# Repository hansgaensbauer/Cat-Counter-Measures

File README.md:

# Cat-Counter-Measures
Counter Cat Countermeasures

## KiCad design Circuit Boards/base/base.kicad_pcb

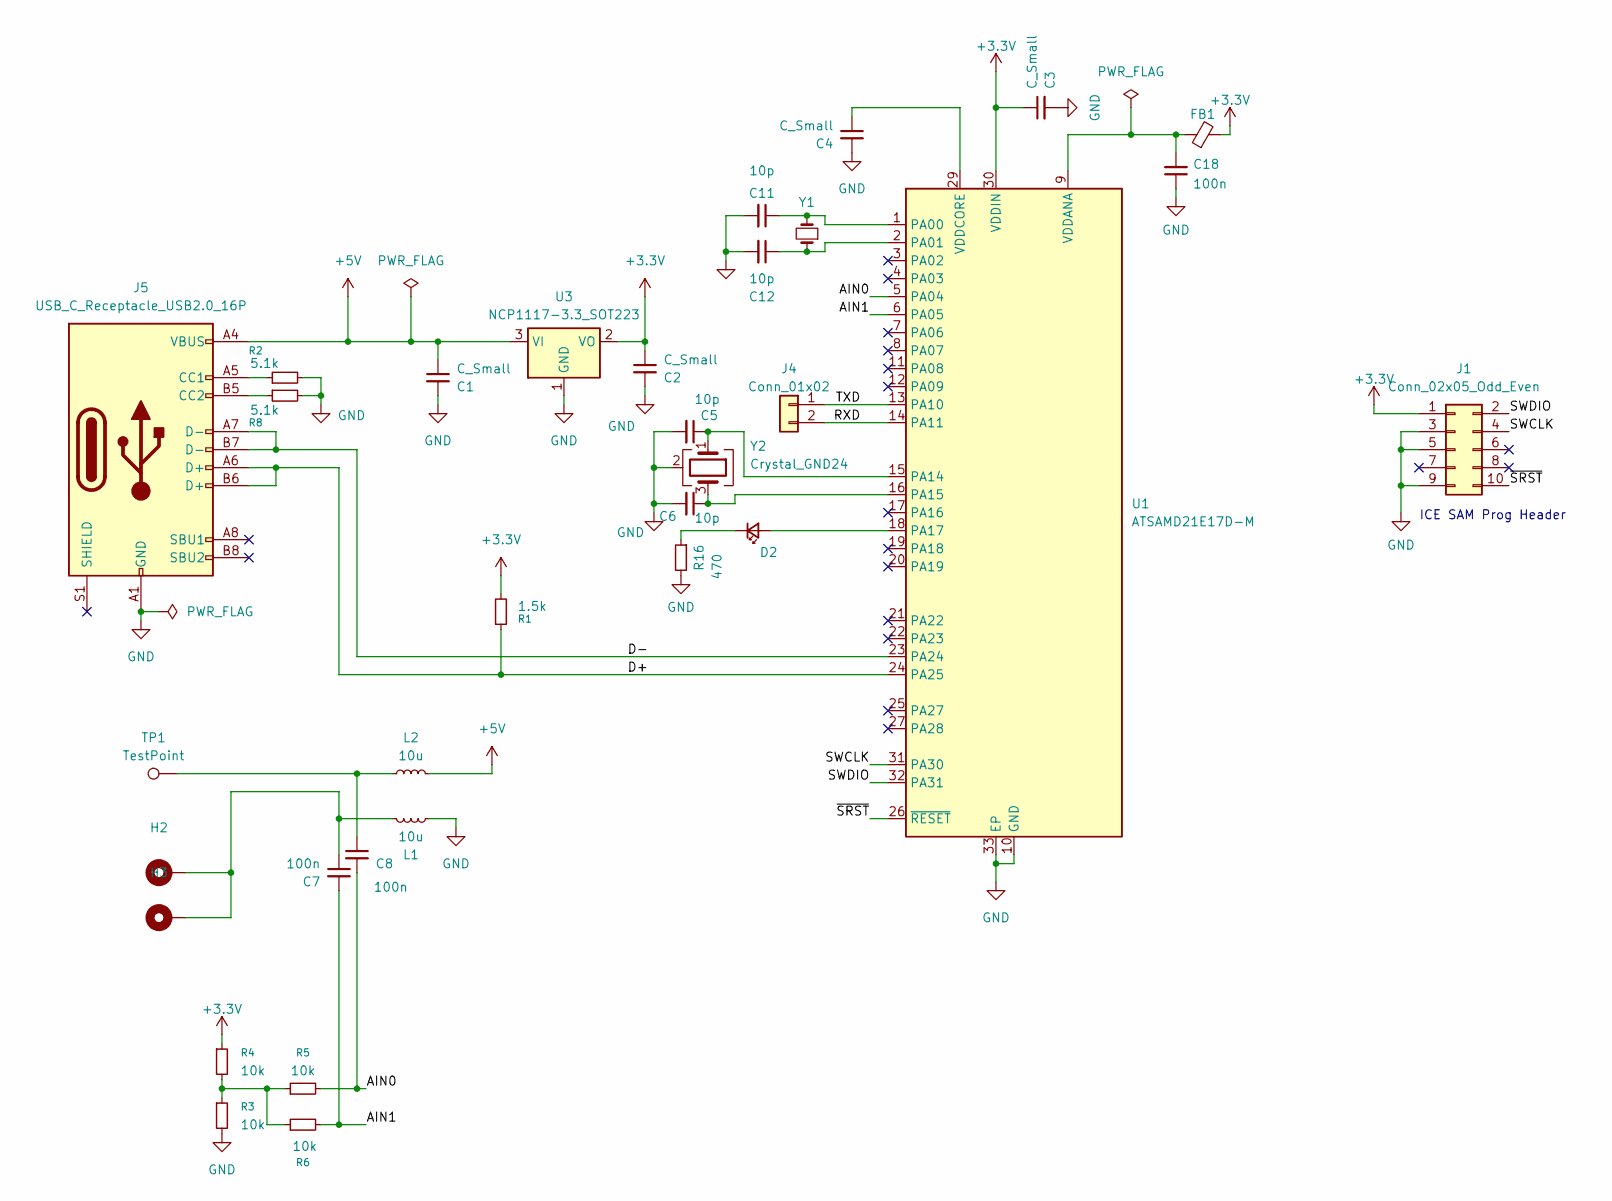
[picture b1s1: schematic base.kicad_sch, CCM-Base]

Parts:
C1, C2, C3, C4: C_Small; C_0603_1608Metric
C5, C6, C11, C12: 10p; C_0603_1608Metric
C7, C8, C18: 100n; C_0603_1608Metric
D2: LED_Small; LED_0805_2012Metric
FB1: FerriteBead_Small; R_0603_1608Metric
H2, H3: MountingHole_Pad; MountingHole_3.2mm_M3_ISO14580_Pad
J1: Conn_02x05_Odd_Even; PinHeader_2x05_P1.27mm_Vertical
J4: Conn_01x02; PinHeader_1x02_P2.54mm_Vertical
J5: USB_C_Receptacle_USB2.0_16P; USB_C_Receptacle_GCT_USB4085
L1, L2: 10u; L_0805_2012Metric
R1: 1.5k; R_0603_1608Metric
R2, R8: 5.1k; R_0603_1608Metric
R3, R4, R5, R6: 10k; R_0603_1608Metric
R16: 470; C_0603_1608Metric
TP1: TestPoint; TestPoint_THTPad_D2.0mm_Drill1.0mm
U1: ATSAMD21E17D-M; QFN-32-1EP_5x5mm_P0.5mm_EP3.6x3.6mm
U3: NCP1117-3.3_SOT223; SOT-223-3_TabPin2
Y1: Crystal_Small; Crystal_SMD_MicroCrystal_CM9V-T1A-2Pin_1.6x1.0mm
Y2: Crystal_GND24; Crystal_SMD_WE_CFPX-180-4Pin_3.2x2.5mm

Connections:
+3.3V: C2.1, C3.1, FB1.2, J1.1, R1.2, R4.1, U1.30 (VDDIN), U3.2 (VO)
+5V: C1.1, J5.A4 (VBUS), J5.A9 (VBUS), J5.B4 (VBUS), J5.B9 (VBUS), L2.1, U3.3 (VI)
/AIN0: C8.2, R5.2, U1.5 (PA04)
/AIN1: C7.2, R6.2, U1.6 (PA05)
/D+: J5.A6 (D+), J5.B6 (D+), R1.1, U1.24 (PA25)
/D-: J5.A7 (D-), J5.B7 (D-), U1.23 (PA24)
/RXD: J4.2, U1.14 (PA11)
/SWCLK: J1.4, U1.31 (PA30)
/SWDIO: J1.2, U1.32 (PA31)
/TXD: J4.1, U1.13 (PA10)
/~SRST: J1.10, U1.26 (~RESET)
GND: C1.2, C2.2, C3.2, C4.2, C5.2, C6.2, C11.2, C12.2, C18.1, J1.3, J1.5, J1.9, J5.A1 (GND), J5.A12 (GND), J5.B1 (GND), J5.B12 (GND), L1.1, R2.2, R3.2, R8.2, R16.2, U1.10 (GND), U1.28 (GND), U1.33 (EP), U3.1 (GND), Y2.2 (G), Y2.4 (G)
unnamed: C7.1, H2.1, H3.1, L1.2
unnamed: C8.1, L2.2, TP1.1
unnamed: D2.2 (A), U1.18 (PA17)
unnamed: D2.1 (K), R16.1
unnamed: J5.A5 (CC1), R2.1
unnamed: J5.B5 (CC2), R8.1
unnamed: R3.1, R4.2, R5.1, R6.1
unnamed: C11.1, U1.1 (PA00), Y1.2
unnamed: C12.1, U1.2 (PA01), Y1.1
unnamed: C5.1, U1.15 (PA14), Y2.1
unnamed: C6.1, U1.16 (PA15), Y2.3
unnamed: C18.2, FB1.1, U1.9 (VDDANA)
unnamed: C4.1, U1.29 (VDDCORE)

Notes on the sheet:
ICE SAM Prog Header

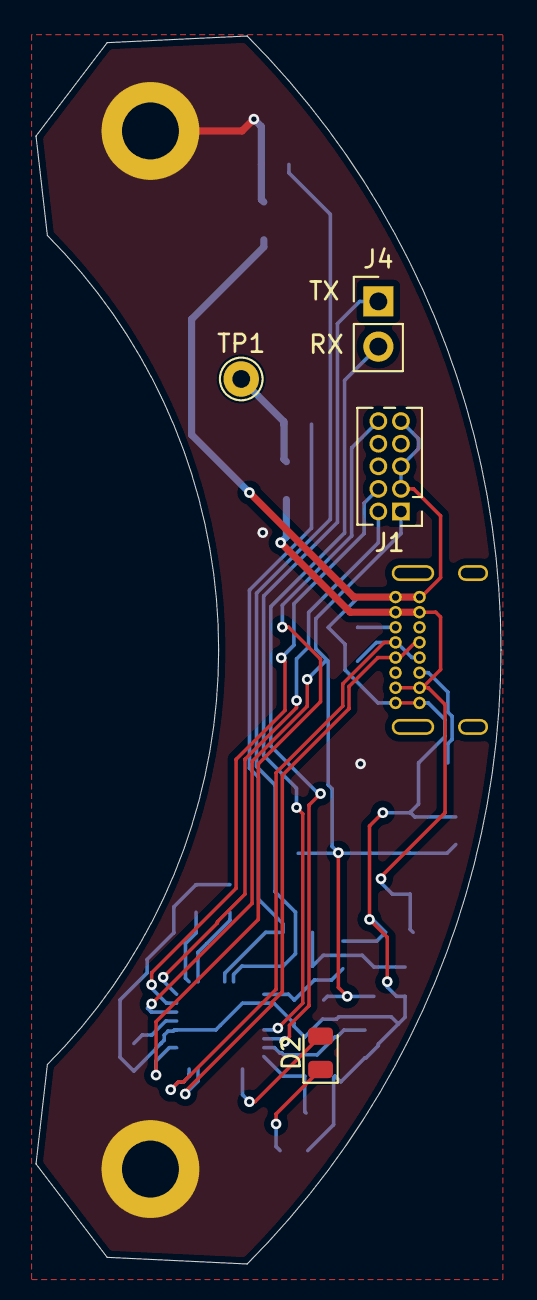
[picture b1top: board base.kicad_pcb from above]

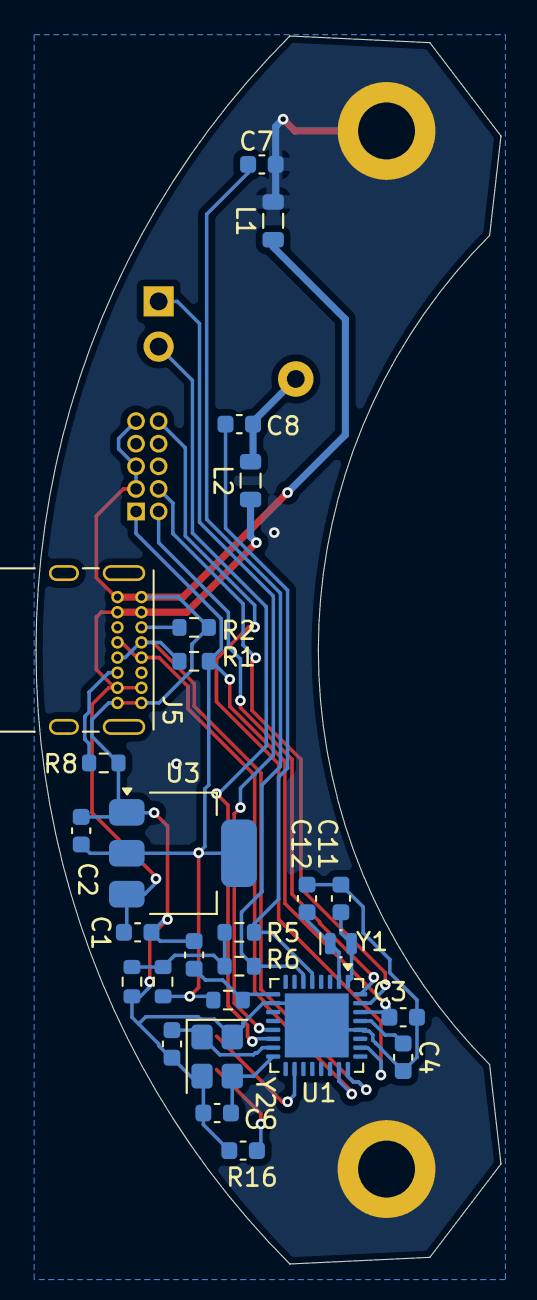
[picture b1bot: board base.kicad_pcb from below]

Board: 2 copper layers, 26.1 x 69.0 mm, 33 parts (27 on the bottom side), 25 nets.

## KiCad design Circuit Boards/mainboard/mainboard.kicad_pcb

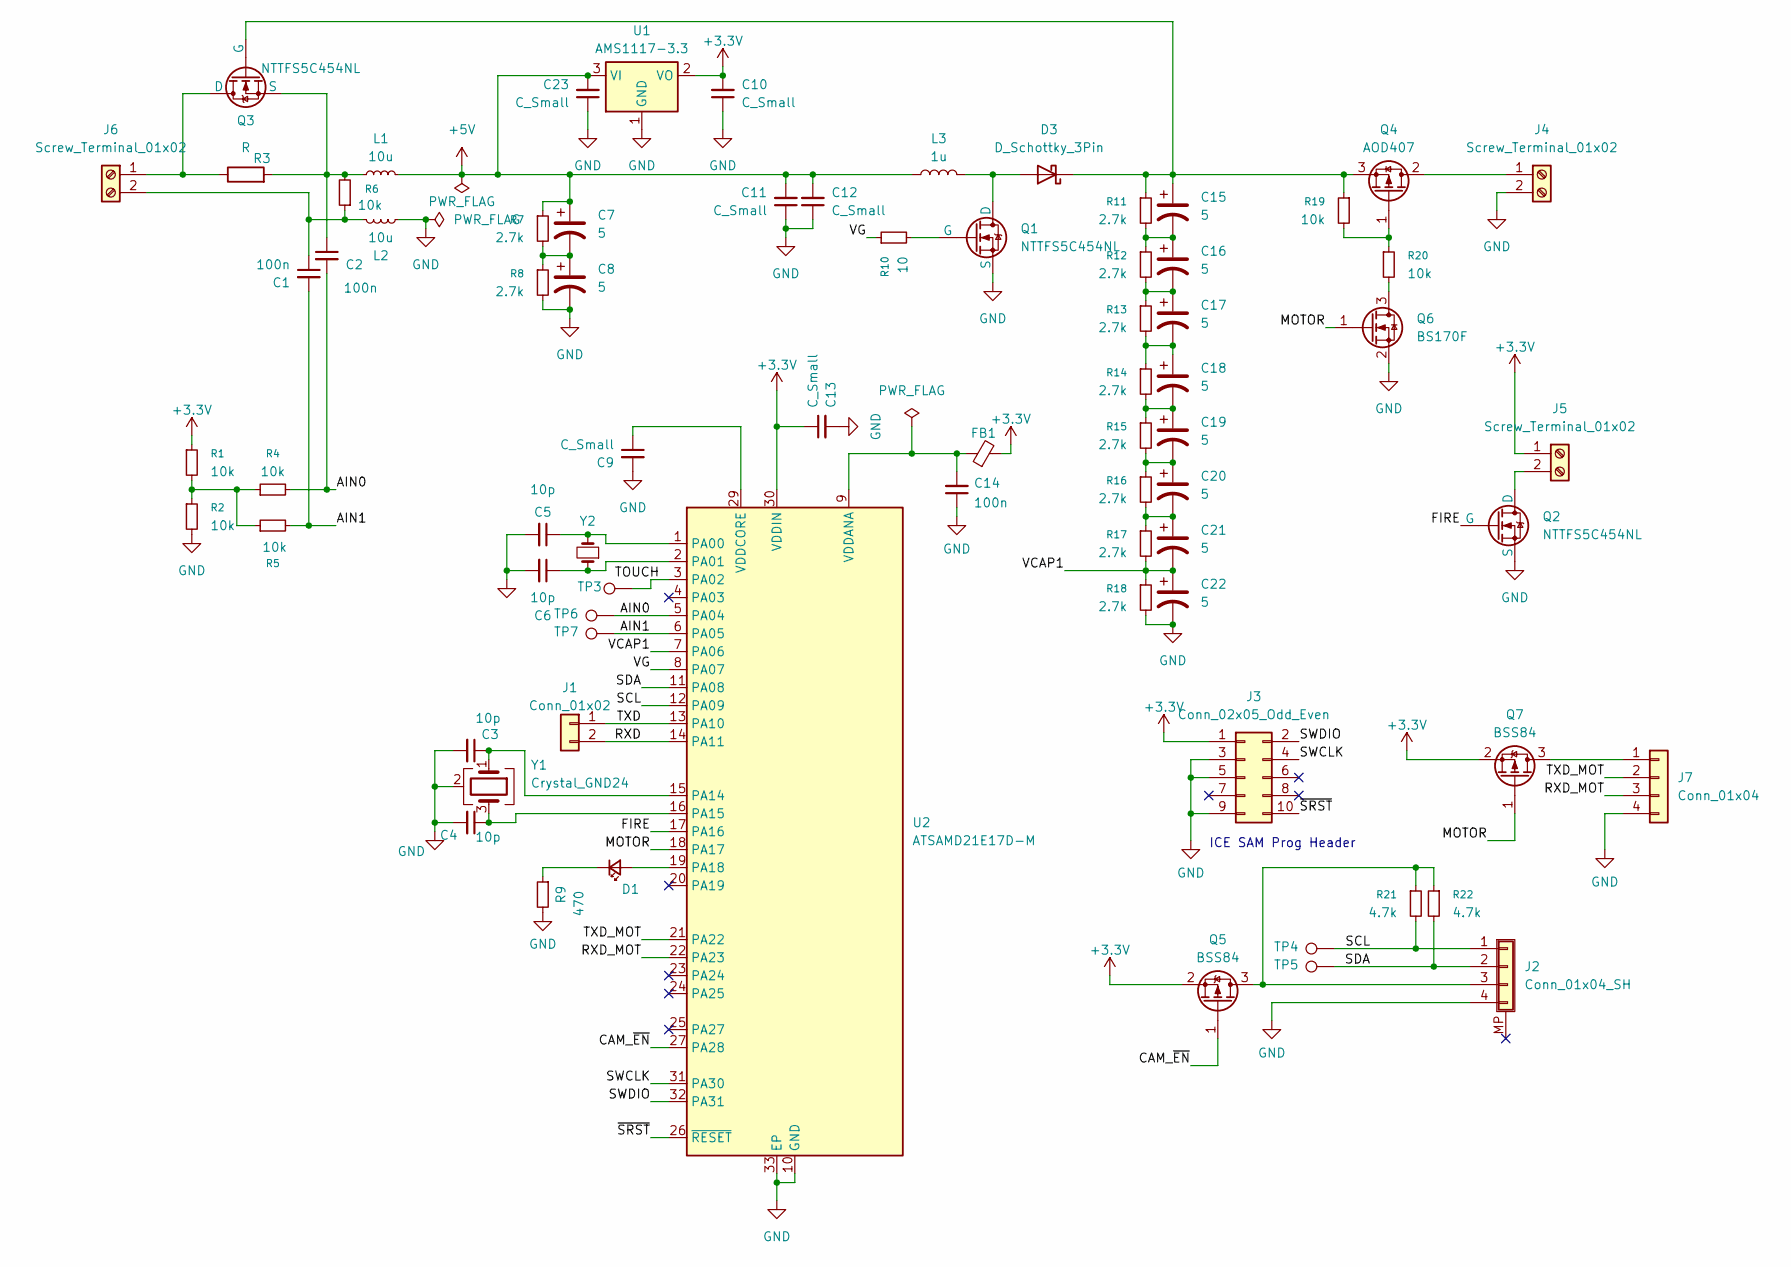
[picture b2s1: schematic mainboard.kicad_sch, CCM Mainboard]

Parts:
C1, C2, C14: 100n; C_0603_1608Metric
C3, C4, C5, C6: 10p; C_0603_1608Metric
C7, C8, C15, C16, C17, C18, C19, C20, C21, C22: 5; CP_Radial_D10.0mm_P5.00mm; MPN BCAP0005 P300 X11
C9, C10, C12, C13, C23: C_Small; C_0603_1608Metric
C11: C_Small; C_0805_2012Metric
D1: LED_Small; LED_0805_2012Metric
D3: D_Schottky_3Pin; PowerDI5; MPN SDT10A45P5
FB1: FerriteBead_Small; R_0603_1608Metric
J1: Conn_01x02; PinHeader_1x02_P2.54mm_Vertical
J2: Conn_01x04_SH; JST_SH_SM04B-SRSS-TB_1x04-1MP_P1.00mm_Horizontal; MPN SM04B-SRSS-TB
J3: Conn_02x05_Odd_Even; PinHeader_2x05_P1.27mm_Vertical
J4: Screw_Terminal_01x02; TerminalBlock_MaiXu_MX126-5.0-02P_1x02_P5.00mm; MPN 691137710002
J5, J6: Screw_Terminal_01x02; JST_XH_B2B-XH-A_1x02_P2.50mm_Vertical; MPN 691137710002
J7: Conn_01x04; JST_XH_B4B-XH-A_1x04_P2.50mm_Vertical
L1, L2: 10u; L_0805_2012Metric
L3: 1u; L_Wuerth_XHMI-6060; MPN 74439344010
Q1, Q2, Q3: NTTFS5C454NL; WDFN8; MPN NTTFS5C454NL
Q4: AOD407; TO-252-2; MPN AOD407
Q5, Q7: BSS84; SOT-23
Q6: BS170F; SOT-23
R1, R2, R4, R5, R6: 10k; R_0603_1608Metric
R3: R; R_2512_6332Metric
R7, R8, R11, R12, R13, R14, R15, R16, R17, R18: 2.7k; C_0603_1608Metric
R9: 470; C_0603_1608Metric
R10: 10; C_0603_1608Metric
R19, R20: 10k; C_0603_1608Metric
R21, R22: 4.7k; C_0603_1608Metric
TP3, TP4, TP5, TP6, TP7: TestPoint; TestPoint_THTPad_D1.5mm_Drill0.7mm
U1: AMS1117-3.3; SOT-223-3_TabPin2
U2: ATSAMD21E17D-M; QFN-32-1EP_5x5mm_P0.5mm_EP3.6x3.6mm
Y1: Crystal_GND24; Crystal_SMD_WE_CFPX-180-4Pin_3.2x2.5mm
Y2: Crystal_Small; Crystal_SMD_MicroCrystal_CM9V-T1A-2Pin_1.6x1.0mm

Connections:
+3.3V: C10.2, C13.1, FB1.2, J3.1, J5.1, Q5.2 (S), Q7.2 (S), R1.1, U1.2 (VO), U2.30 (VDDIN)
+5V: C7.1, C11.2, C12.2, C23.2, L1.1, L3.1, R7.1, U1.3 (VI)
/AIN0: C2.2, R4.2, TP6.1, U2.5 (PA04)
/AIN1: C1.2, R5.2, TP7.1, U2.6 (PA05)
/CAM_~EN: Q5.1 (G), U2.27 (PA28)
/FIRE: Q2.4 (G), U2.17 (PA16)
/MOTOR: Q6.1 (G), Q7.1 (G), U2.18 (PA17)
/RXD: J1.2, U2.14 (PA11)
/RXD_MOT: J7.3, U2.22 (PA23)
/SCL: J2.1, R21.2, TP4.1, U2.12 (PA09)
/SDA: J2.2, R22.2, TP5.1, U2.11 (PA08)
/SWCLK: J3.4, U2.31 (PA30)
/SWDIO: J3.2, U2.32 (PA31)
/TOUCH: TP3.1, U2.3 (PA02)
/TXD: J1.1, U2.13 (PA10)
/TXD_MOT: J7.2, U2.21 (PA22)
/VCAP1: C21.2, C22.1, R17.2, R18.1, U2.7 (PA06)
/VG: R10.1, U2.8 (PA07)
/~SRST: J3.10, U2.26 (~RESET)
GND: C3.2, C4.2, C5.2, C6.2, C8.2, C9.2, C10.1, C11.1, C12.1, C13.2, C14.1, C22.2, C23.1, J2.4, J3.3, J3.5, J3.9, J4.2, J7.4, L2.1, Q1.1 (S), Q1.2, Q1.3, Q2.1 (S), Q2.2, Q2.3, Q6.2 (S), R2.2, R8.2, R9.2, R18.2, U1.1 (GND), U2.10 (GND), U2.28 (GND), U2.33 (EP), Y1.2 (G), Y1.4 (G)
unnamed: C7.2, C8.1, R7.2, R8.1
unnamed: C15.2, C16.1, R11.2, R12.1
unnamed: C16.2, C17.1, R12.2, R13.1
unnamed: C17.2, C18.1, R13.2, R14.1
unnamed: C18.2, C19.1, R14.2, R15.1
unnamed: C19.2, C20.1, R15.2, R16.1
unnamed: C20.2, C21.1, R16.2, R17.1
unnamed: D1.2 (A), U2.19 (PA18)
unnamed: D1.1 (K), R9.1
unnamed: D3.2 (A), D3.3, L3.2, Q1.5 (D)
unnamed: C15.1, D3.1 (K), Q3.4 (G), Q4.3 (S), R11.1, R19.1
unnamed: J2.3, Q5.3 (D), R21.1, R22.1
unnamed: J4.1, Q4.2 (D)
unnamed: J5.2, Q2.5 (D)
unnamed: J6.1, Q3.5 (D), R3.1
unnamed: C1.1, J6.2, L2.2, R6.1
unnamed: J7.1, Q7.3 (D)
unnamed: Q1.4 (G), R10.2
unnamed: C2.1, L1.2, Q3.1 (S), Q3.2, Q3.3, R3.2, R6.2
unnamed: Q4.1 (G), R19.2, R20.1
unnamed: Q6.3 (D), R20.2
unnamed: R1.2, R2.1, R4.1, R5.1
unnamed: C5.1, U2.1 (PA00), Y2.2
unnamed: C6.1, U2.2 (PA01), Y2.1
unnamed: C3.1, U2.15 (PA14), Y1.1
unnamed: C4.1, U2.16 (PA15), Y1.3
unnamed: C14.2, FB1.1, U2.9 (VDDANA)
unnamed: C9.1, U2.29 (VDDCORE)

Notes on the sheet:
ICE SAM Prog Header

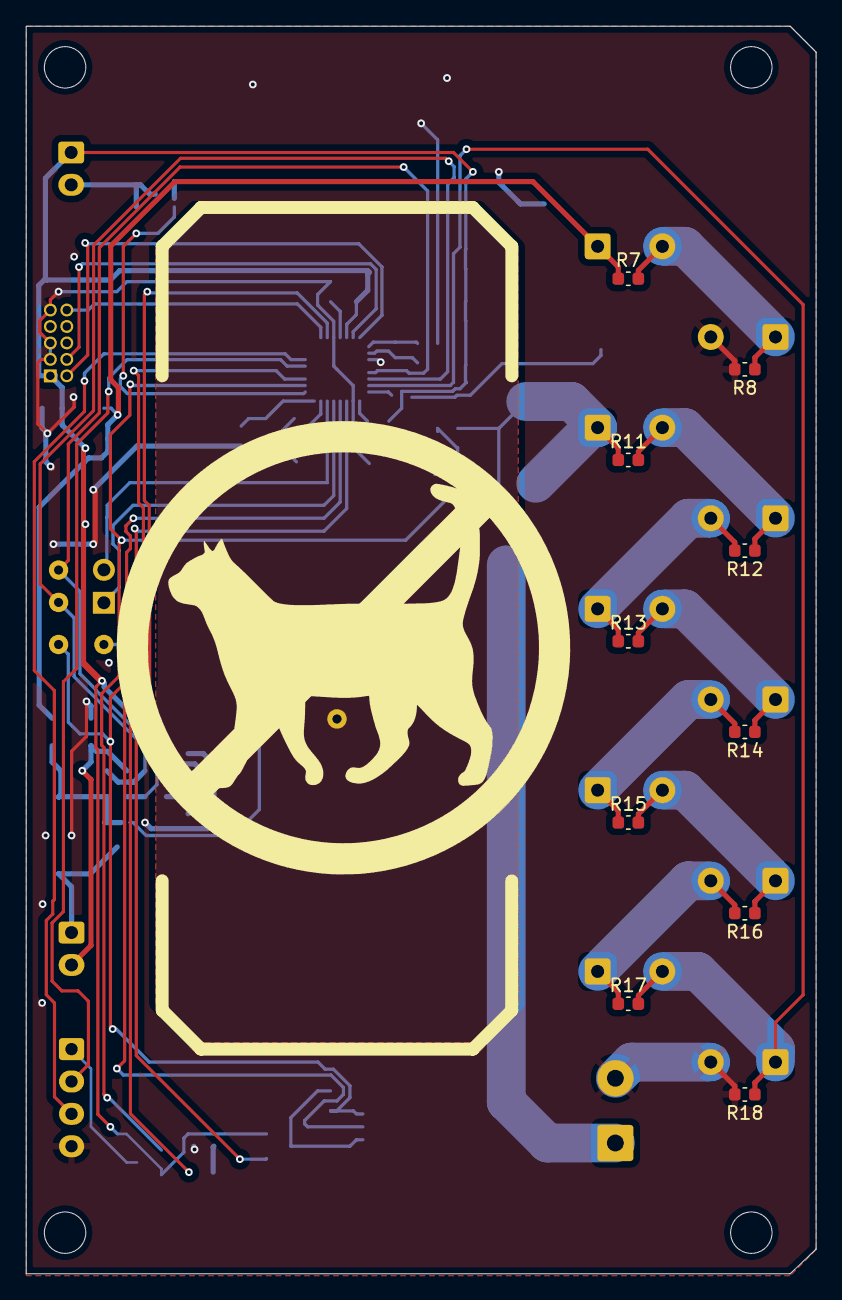
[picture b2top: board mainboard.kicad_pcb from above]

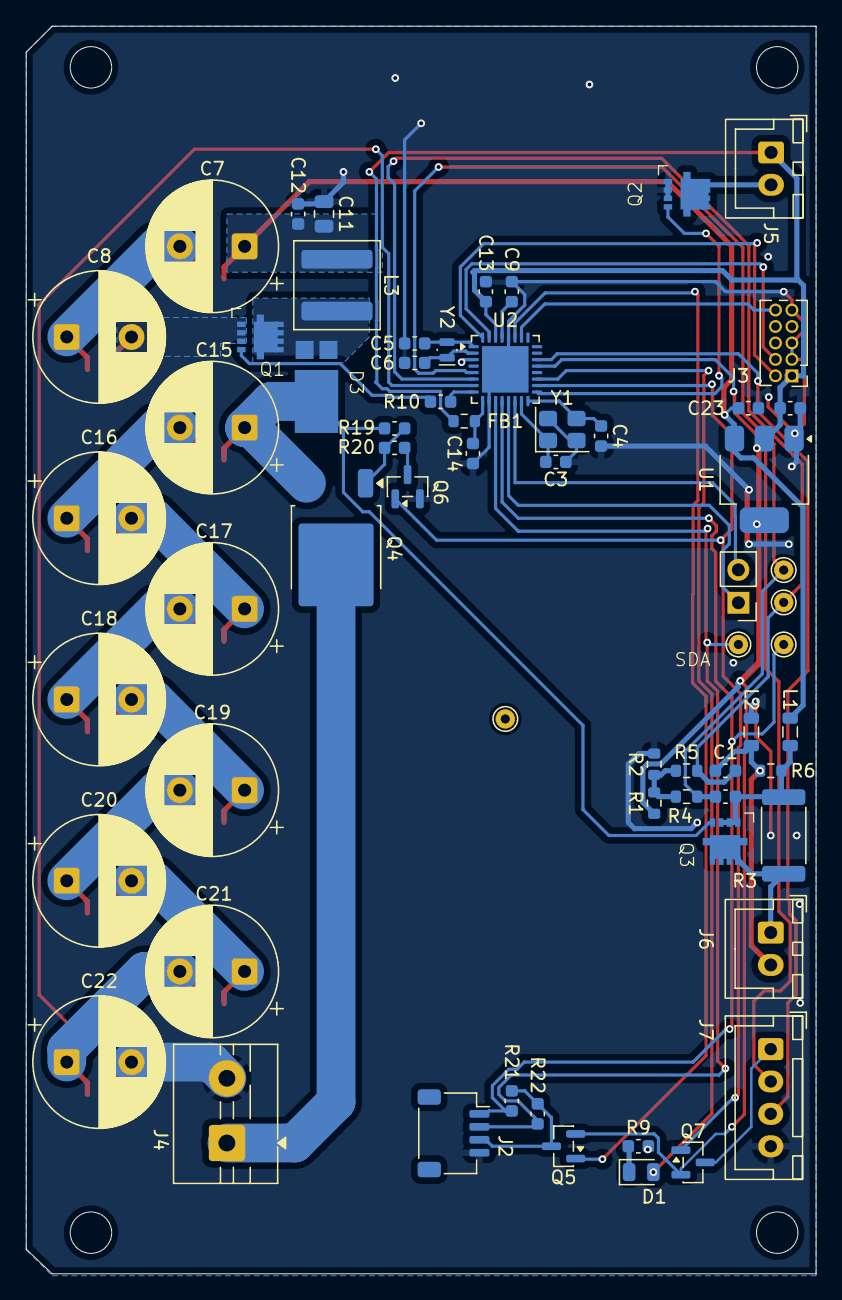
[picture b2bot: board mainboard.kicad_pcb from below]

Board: 2 copper layers, 61.0 x 96.3 mm, 74 parts (64 on the bottom side), 48 nets.

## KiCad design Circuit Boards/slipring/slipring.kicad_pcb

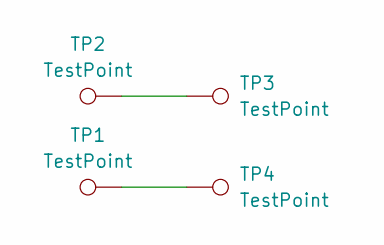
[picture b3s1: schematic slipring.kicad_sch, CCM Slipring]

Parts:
TP1, TP2: TestPoint; ring
TP3, TP4: TestPoint; TestPoint_Pad_3.0x3.0mm

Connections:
unnamed: TP1.1, TP4.1
unnamed: TP2.1, TP3.1

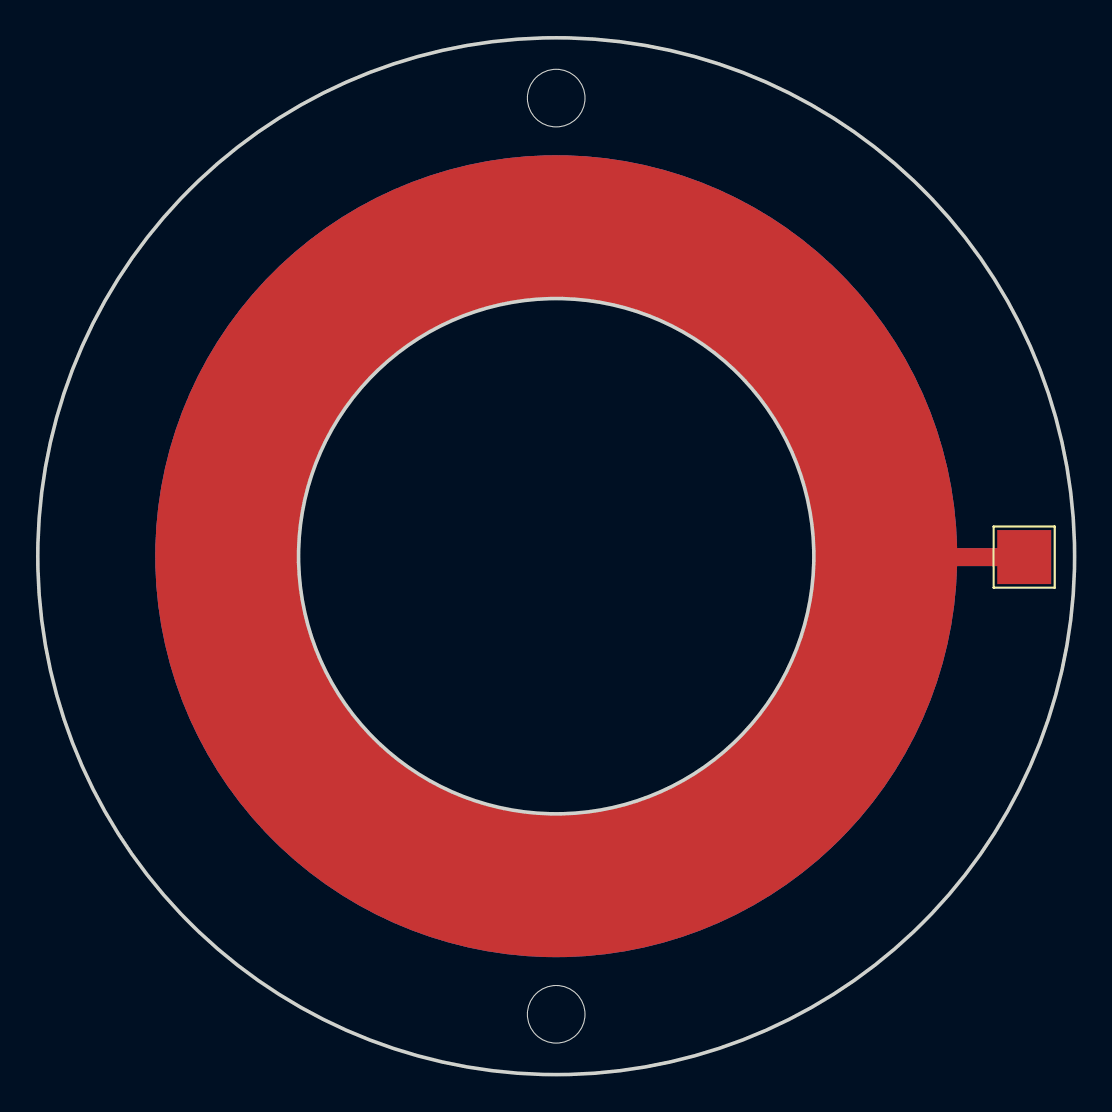
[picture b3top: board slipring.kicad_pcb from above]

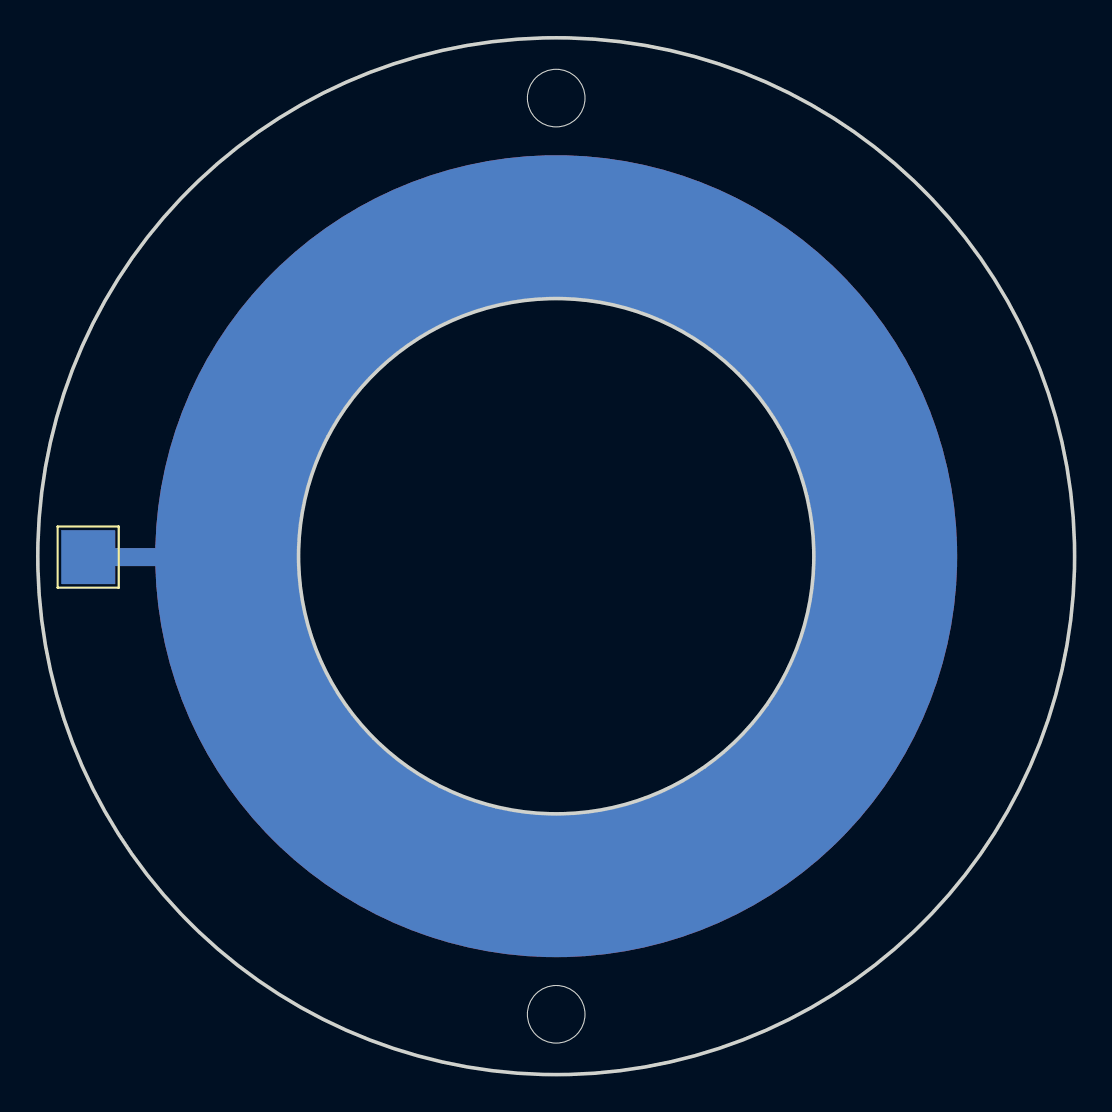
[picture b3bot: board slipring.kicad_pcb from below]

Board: 2 copper layers, 57.6 x 57.6 mm, 4 parts (2 on the bottom side), 2 nets.

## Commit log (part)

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2026-03-06 Add circuit boards
2026-06-24 TinyUSB working
2026-06-24 Update gitignore
2026-06-28 Update gitmodules
2026-06-28 Fix tinyusb path
2026-06-29 Working minimal uart
2026-06-30 I2C reads working
